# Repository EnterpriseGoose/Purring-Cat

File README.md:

# Purring Cat

This is a cute little cat that will purr (vibrate) when you pet it's back (by pushing a button). It also will light up the eyes.

## Screenshots

## BOM
- 1x Battery Holder
- 1x Push Button
- 2x LED
- 1x Vibration Motor
- 3x 220 Resistor

Made by @enterprisegoose (@Olive) on slack!

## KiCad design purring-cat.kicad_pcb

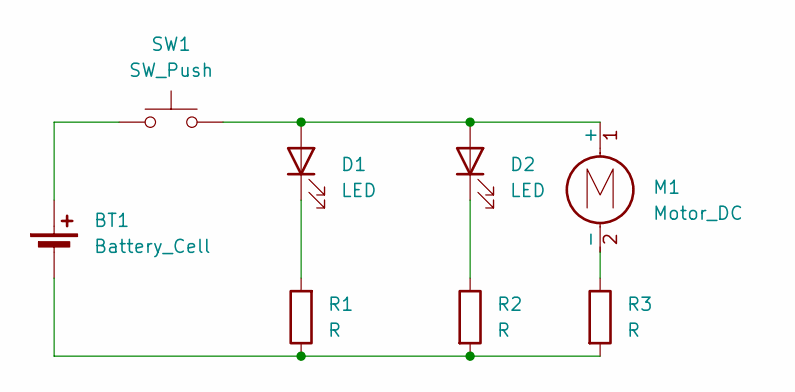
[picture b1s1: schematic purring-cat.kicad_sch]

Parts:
BT1: Battery_Cell; BatteryHolder_Keystone_3034_1x20mm
D1, D2: LED; LED_D5.0mm
M1: Motor_DC; PinHeader_1x02_P2.54mm_Vertical
R1, R2, R3: R; R_Axial_DIN0207_L6.3mm_D2.5mm_P7.62mm_Horizontal
SW1: SW_Push; SW_PUSH_6mm

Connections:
unnamed: BT1.1 (+), SW1.1
unnamed: BT1.2 (-), R1.1, R2.2, R3.2
unnamed: D1.2 (A), D2.2 (A), M1.1 (+), SW1.2
unnamed: D1.1 (K), R1.2
unnamed: D2.1 (K), R2.1
unnamed: M1.2 (-), R3.1

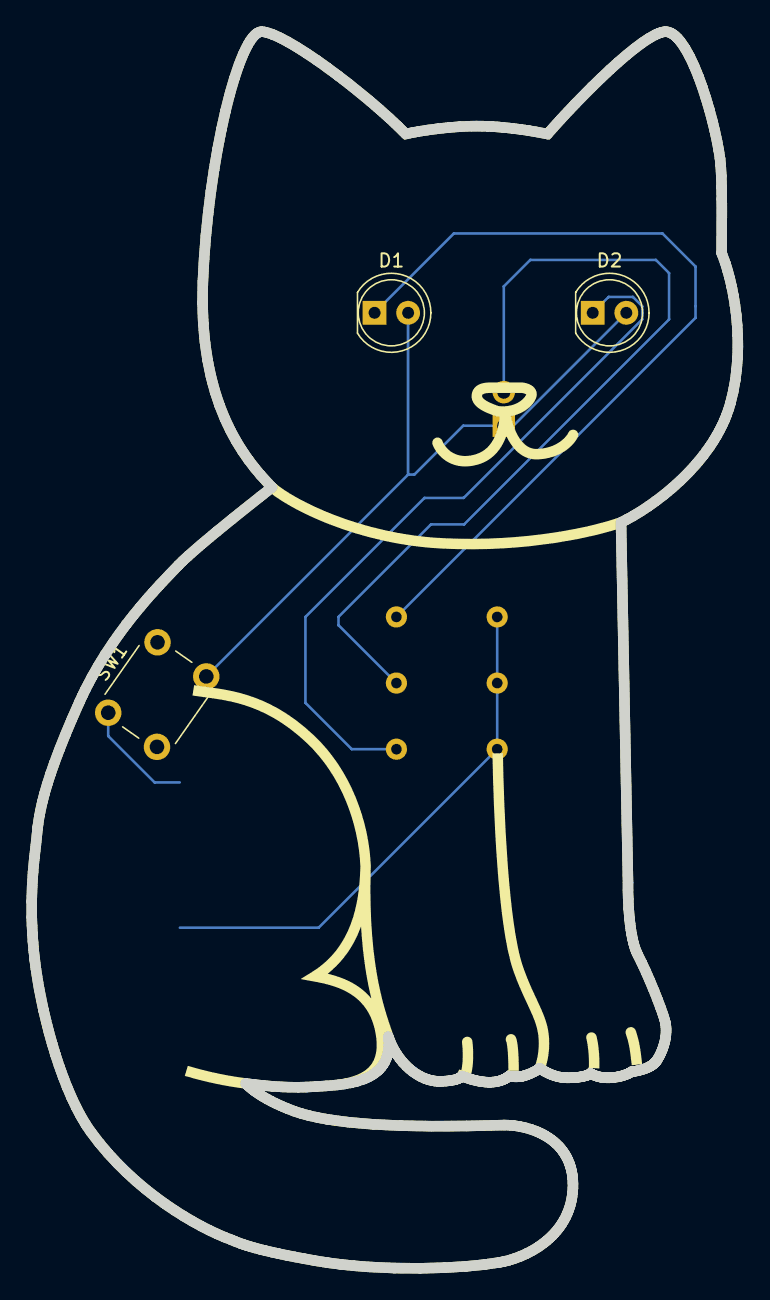
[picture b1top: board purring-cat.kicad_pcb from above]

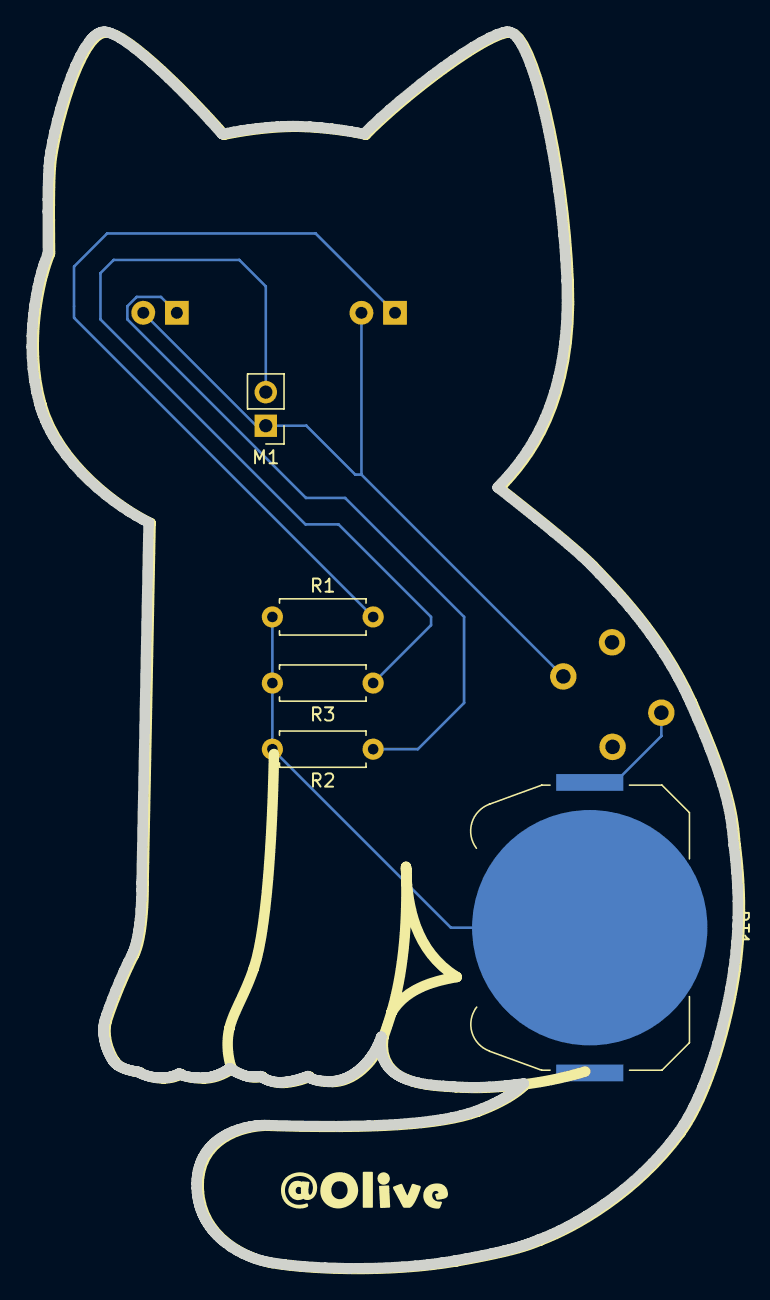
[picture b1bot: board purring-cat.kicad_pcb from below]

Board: 2 copper layers, 53.4 x 93.5 mm, 8 parts (5 on the bottom side), 6 nets.

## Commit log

2025-06-08 Add KiCAD files
2025-06-09 Add backside of cat
